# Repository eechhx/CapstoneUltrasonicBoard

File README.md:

# CapstoneUltrasonicBoard
PCB for Ultrasonic Board

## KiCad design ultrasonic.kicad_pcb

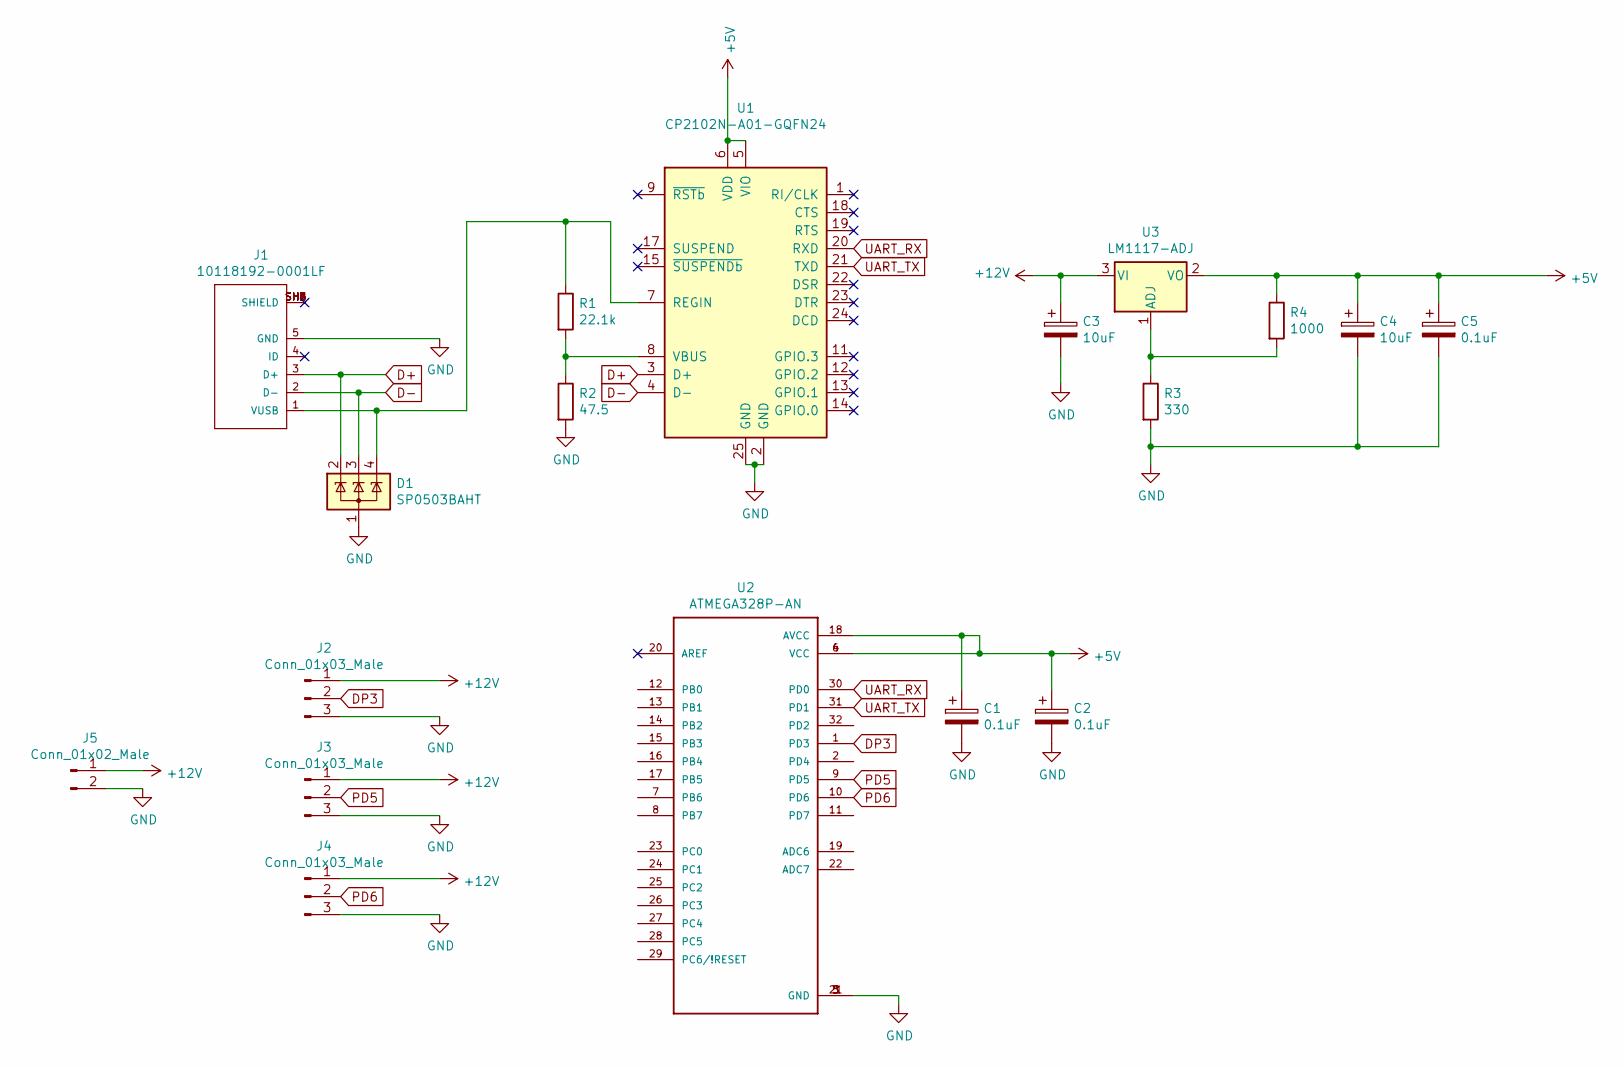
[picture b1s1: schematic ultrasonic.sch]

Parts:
C1, C2, C5: 0.1uF; C_0805_2012Metric_Pad1.15x1.40mm_HandSolder
C3, C4: 10uF; C_0805_2012Metric_Pad1.15x1.40mm_HandSolder
D1: SP0503BAHT; SOT-143
J1: 10118192-0001LF; AMPHENOL_10118192-0001LF
J2, J3, J4: Conn_01x03_Male; Molex_SL_171971-0003_1x03_P2.54mm_Vertical
J5: Conn_01x02_Male; Molex_SL_171971-0002_1x02_P2.54mm_Vertical
R1: 22.1k; R_0805_2012Metric_Pad1.15x1.40mm_HandSolder
R2: 47.5; R_0805_2012Metric_Pad1.15x1.40mm_HandSolder
R3: 330; R_0805_2012Metric_Pad1.15x1.40mm_HandSolder
R4: 1000; R_0805_2012Metric_Pad1.15x1.40mm_HandSolder
U1: CP2102N-A01-GQFN24; QFN-24-1EP_4x4mm_P0.5mm_EP2.6x2.6mm
U2: ATMEGA328P-AN; QFP80P900X900X120-32N
U3: LM1117-ADJ; SOT-223-3_TabPin2

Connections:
+5V: C1.1, C2.1, C4.1, C5.1, R4.1, U1.5 (VIO), U1.6 (VDD), U2.4 (VCC), U2.6 (VCC), U2.18 (AVCC), U3.2 (VO)
+12V: C3.1, J2.1, J3.1, J4.1, J5.1, U3.3 (VI)
D+: D1.2 (K), J1.3 (D+), U1.3 (D+)
D-: D1.3 (K), J1.2 (D-), U1.4 (D-)
DP3: J2.2, U2.1 (PD3)
GND: C1.2, C2.2, C3.2, C4.2, C5.2, D1.1 (A), J1.5 (GND), J2.3, J3.3, J4.3, J5.2, R2.2, R3.2, U1.2 (GND), U1.25 (GND), U2.3 (GND), U2.5 (GND), U2.21 (GND)
unnamed: D1.4 (K), J1.1 (VUSB), R1.1, U1.7 (REGIN)
unnamed: J1.SH1 (SHIELD), J1.SH2 (SHIELD), J1.SH3 (SHIELD), J1.SH4 (SHIELD), J1.SH5 (SHIELD), J1.SH6 (SHIELD)
unnamed: R1.2, R2.1, U1.8 (VBUS)
unnamed: R3.1, R4.2, U3.1 (ADJ)
PD5: J3.2, U2.9 (PD5)
PD6: J4.2, U2.10 (PD6)
UART_RX: U1.20 (RXD), U2.30 (PD0)
UART_TX: U1.21 (TXD), U2.31 (PD1)

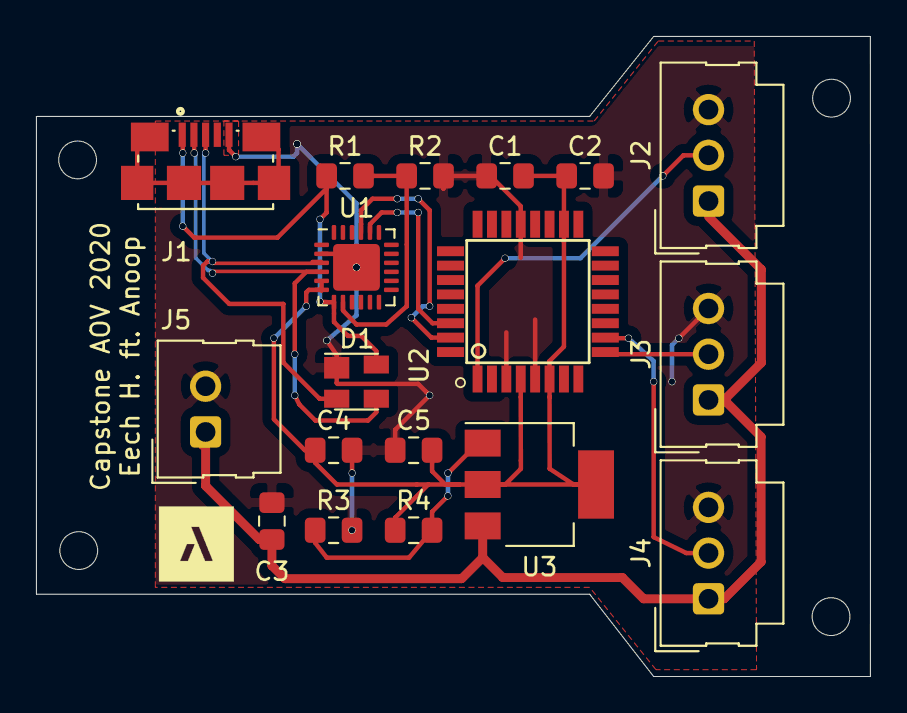
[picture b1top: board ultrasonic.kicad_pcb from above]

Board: 2 copper layers, 46.3 x 35.6 mm, 18 parts (0 on the bottom side), 14 nets.

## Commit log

2020-02-05 Initial Commit of Ultrasonic Board for Capstone
2020-02-05 Added connectors for ultrasonic
2020-02-05 Revision 1
2020-02-05 Final Rev 1
2020-02-07 Adjusted USB Connector
